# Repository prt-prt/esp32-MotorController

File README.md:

# ESP32 Motor Controller

A collection of motor control implementations for the ESP32-S2 Mini with DRV8833 motor driver.

## Version Overview

### v1: Basic Test
- Simple motor test sequence
- Basic forward/backward/turn movements
- No fault detection

### v2: Mode System
- Multiple movement modes (wander, rotate, test)
- Mode switching logic
- Basic error handling

### v3: Power Management
- Improved power handling
- Speed ramping
- Basic fault detection
- Reduced motor speeds

### v4: Organic Movement
- Slow, rock-like movement patterns
- Advanced fault detection
- PWM-based motor control
- Random movement generation
- Detailed debugging

### v5: Simple Forward Test
- Continuous forward movement
- Basic PWM control
- Minimal code for testing
- No mode switching or complex logic

### v6: All Directions Test
- Tests all motor directions sequentially
- Basic PWM control
- Auxiliary pin control (GPIO39)
- Cycle between directions automatically

## Hardware
- ESP32-S2 Mini (Lolin)
- DRV8833 Motor Driver
- 2 DC Motors
- Power Supply (5V recommended)

## Pin Configuration
- Motor A: GPIO11 (IN1), GPIO9 (IN2)
- Motor B: GPIO7 (IN1), GPIO5 (IN2)
- Fault Pin: GPIO12
- LED: GPIO15

## Project Structure

This project is organized into two versions:
- **v1**: Uses the ESP32-CAM and L298N motor driver (older, traditional driver)
- **v2**: Uses the ESP32-S2 Mini and DRV8833 motor driver (more efficient, modern setup)

Each version contains its own complete implementation for its respective hardware. For detailed wiring and implementation specifics, see the WIRING.md file in each subproject folder.

## Hardware Requirements

### Common Components for Both Versions
- 2-wheel drive robot car chassis with DC motors
- Jumper wires
- Small breadboard (optional, for cleaner wiring)

### Version Specific Components
- **v1**: 
  - ESP32-CAM development board
  - L298N dual H-bridge motor driver ([detailed documentation](v1/WIRING.md))
  - MP1584EN buck converter module (for power regulation)
  - Power supply for motors (battery pack/power bank)

- **v2**: 
  - Wemos ESP32-S2 Mini development board
  - DRV8833 dual H-bridge motor driver ([detailed documentation](v2/WIRING.md))
  - 5V powerbank with USB output
  - USB splitter/hub or adapter
  - USB in-line power switch (for global power control)
  - Step-up converter (boosts 5V from powerbank to 6V for motors)

### Power Supply Architecture Differences

The v1 and v2 versions use different power supply approaches:

**v1 Power Supply:**
- Battery/power source → MP1584EN buck converter → ESP32-CAM (5V)
- Battery/power source → L298N motor driver (higher voltage)

**v2 Power Supply:**
- Powerbank USB output → Global power switch → USB splitter/hub
  - First output: USB-C connection to ESP32-S2 Mini (direct connection)
  - Second output: 5V to Step-up converter → DRV8833 motor driver (6V)

The v2 setup uses a true global power switch that controls the entire system with a single switch, turning both the microcontroller and motors on/off together.

## Hardware Comparison

### Microcontroller Comparison
| Feature | v1: ESP32-CAM | v2: ESP32-S2 Mini |
|---------|--------------|-------------------|
| USB Connection | External programmer required | Built-in USB-C port |
| Size | Larger | Compact |
| Power Input | 5V via pins | Direct USB-C |
| Programming | Via serial adapter | Native USB |
| Unnecessary Features | Camera module | None |
| Form Factor | Less robot-friendly | Ideal for robotics |

### Motor Driver Comparison
| Feature | v1: L298N | v2: DRV8833 |
|---------|----------|-------------|
| Efficiency | ~70% | >90% |
| Control Pins | 6 total | 4 total |
| Heat Generation | High | Low |
| Size | Large | Compact |
| Control Method | Enable + Direction pins | PWM on all pins |

### Power Control Comparison
| Feature | v1 Approach | v2 Approach |
|---------|------------|-------------|
| Power Switch | Controls motors only | True global control (entire system) |
| Power Source | Separate paths | Single source with distribution |
| Wiring Complexity | More complex | Simplified with USB connectivity |
| Development Mode | ESP32 always on | System fully controlled by one switch |

For detailed pin connections, wiring diagrams, and implementation specifics, see:
- [L298N Wiring & Implementation Guide](v1/WIRING.md)
- [DRV8833 Wiring & Implementation Guide](v2/WIRING.md)

## Software Setup

This project uses PlatformIO for development and deployment:

1. Install [Visual Studio Code](https://code.visualstudio.com/)
2. Install the [PlatformIO extension](https://platformio.org/install/ide?install=vscode)
3. Clone or download this repository
4. Open either the v1 or v2 project folder in VS Code
5. Build and upload the project using PlatformIO

### V2 Programming Advantage
The v2 version with ESP32-S2 Mini can be programmed directly via USB-C connection without additional hardware, making development and testing significantly easier. During development, you can disconnect the powerbank and connect the ESP32-S2 Mini directly to your computer.

## Features

### Movement Modes

The robot car supports three different movement modes:

1. **Test Mode**: Demonstrates basic movements in a sequence
2. **Wander Mode**: Robot randomly wanders with organic movements
3. **Rotate Mode**: Robot slowly rotates around its axis

By default, the robot switches between Wander Mode and Rotate Mode every 30 seconds.

### Basic Movement Functions

The code includes the following standard movement functions:

- `moveForward(speed)`: Moves the robot forward
- `moveBackward(speed)`: Moves the robot backward
- `turnLeft(speed)`: Turns the robot left
- `turnRight(speed)`: Turns the robot right
- `stopMotors()`: Stops all motor movement

### Differential Steering

Advanced movement control is achieved through differential steering:

- `moveDifferential(leftSpeed, rightSpeed)`: Allows independent control of each wheel
- `curveLeft(leftSpeed, rightSpeed)`: Creates curved left movement
- `curveRight(leftSpeed, rightSpeed)`: Creates curved right movement

### Speed Control

All movement functions support variable speed control through PWM, with speed values ranging from 0 (stop) to 255 (full speed).

## Movement Modes in Detail

### Test Mode

Cycles through a series of basic movements to test motor functionality:
1. Forward → Stop → Backward → Stop → Left turn → Stop → Right turn → Stop

### Wander Mode

Implements organic, randomized movement with varying speeds and paths:
- Straight forward movement
- Gentle left and right curves
- Sharp left and right curves
- 180° spin turns
- Backward movement
- Random stops

### Rotate Mode

Performs a slow, controlled rotation around the robot's center:
- Rotates in a random direction (left or right)
- Changes direction every 10 seconds
- Uses reduced speed for careful rotation

## Customization

You can customize the pin assignments at the beginning of the `motor_control.cpp` file if you need to use different GPIO pins on your microcontroller.

To implement additional movement modes or alter the existing ones, refer to the corresponding mode files in the `src` directory.

## Troubleshooting

Basic troubleshooting tips are included in the WIRING.md file for each version:
- [L298N Troubleshooting](v1/WIRING.md#troubleshooting)
- [DRV8833 Troubleshooting](v2/WIRING.md#troubleshooting)

## Project Structure

For each version (v1 and v2):
- `platformio.ini`: PlatformIO configuration
- `WIRING.md`: Detailed wiring and implementation documentation
- `include/motor_control.h`: Header file for motor control functions
- `include/movement_modes.h`: Defines the movement modes enum
- `include/test_mode.h`: Header for test mode
- `include/wander_mode.h`: Header for wander mode
- `include/rotate_mode.h`: Header for rotate mode
- `src/motor_control.cpp`: Motor control functions implementation
- `src/main.cpp`: Main program with setup, loop, and mode switching logic
- `src/test_mode.cpp`: Test mode implementation
- `src/wander_mode.cpp`: Wander mode implementation with organic movement
- `src/rotate_mode.cpp`: Rotate mode implementation

## License

This project is open source and available under the MIT License.

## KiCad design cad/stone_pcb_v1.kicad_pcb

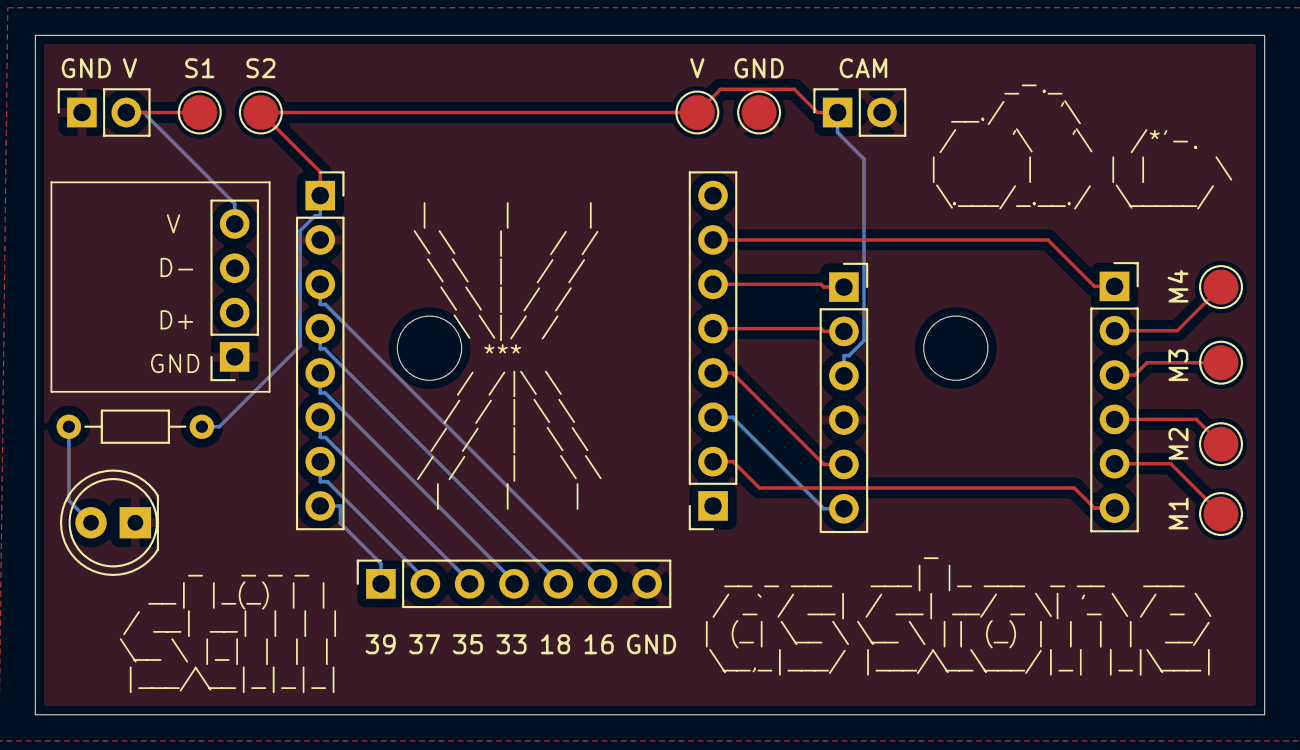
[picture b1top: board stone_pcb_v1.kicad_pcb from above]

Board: 2 copper layers, 70.4 x 38.9 mm, 18 parts (0 on the bottom side), 20 nets.

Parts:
CAM: Conn_01x02_Socket 5V & GND CAMLINE; PinSocket_1x02_P2.54mm_Vertical
D1: LED; LED_D5.0mm
J1: PinSocket_1x06_P2.54mm_Vertical
J2: DRV8833; PinSocket_1x06_P2.54mm_Vertical
J3: Conn_01x04_Socket; PinSocket_1x04_P2.54mm_Vertical
J6, J8: S2-Mini; PinSocket_1x08_P2.54mm_Vertical
J7: Breakouts; PinSocket_1x07_P2.54mm_Vertical
J9: Conn_01x02_Socket EXT_5V & GND; PinSocket_1x02_P2.54mm_Vertical
M1: TP Motor1; TestPoint_Pad_D2.0mm
M2: TP Motor2; TestPoint_Pad_D2.0mm
M3: TP Motor3; TestPoint_Pad_D2.0mm
M4: TP Motor4; TestPoint_Pad_D2.0mm
R2: R; R_Axial_DIN0204_L3.6mm_D1.6mm_P7.62mm_Horizontal
TP5: TP Ground; TestPoint_Pad_D2.0mm
TP6: TP VBUS; TestPoint_Pad_D2.0mm
TP7: S1; TestPoint_Pad_D2.0mm
TP8: S2; TestPoint_Pad_D2.0mm

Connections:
/GND: CAM.2, D1.1 (K), J2.4, J3.1, J6.2, J7.7, J9.1, TP5.1
/VBUS: J3.4, J9.2, TP7.1
unnamed: D1.2 (A), R2.1
unnamed: J1.1, J8.7
unnamed: J1.2, M4.1
unnamed: J1.3, M3.1
unnamed: J1.4, M2.1
unnamed: J1.5, M1.1
unnamed: J1.6, J8.2
unnamed: J2.1, J8.6
unnamed: J2.2, J8.5
unnamed: J2.5, J8.4
unnamed: J2.6, J8.3
unnamed: J6.3, J7.6
unnamed: J6.4, J7.5
unnamed: J6.5, J7.4
unnamed: J6.6, J7.3
unnamed: J6.7, J7.2
unnamed: J6.8, J7.1
unnamed: CAM.1, J2.3, J6.1, R2.2, TP6.1, TP8.1

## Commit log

2025-03-05 first working demo
2025-03-05 more movement modes
2025-03-05 PWM speed controll, code more modular
2025-03-05 refactor to new hardware
2025-03-12 moved code to subdirectory (v1)
2025-03-12 modified both subprojects
2025-03-13 changes to documentation
2025-03-13 changes to hardware, added dimensions_diagram
2025-03-13 added pinout graphic
2025-03-13 changes to wiring
2025-03-13 updates to documentation
2025-04-08 added pcb project
2025-04-08 moved files
2025-04-09 modified pcb
2025-04-09 changes to pcb
2025-04-14 finished pcb design
2025-04-14 updated pcb
2025-05-10 added v5, motor direction test
2025-05-18 changes to v6
2025-05-20 added bootup delay
